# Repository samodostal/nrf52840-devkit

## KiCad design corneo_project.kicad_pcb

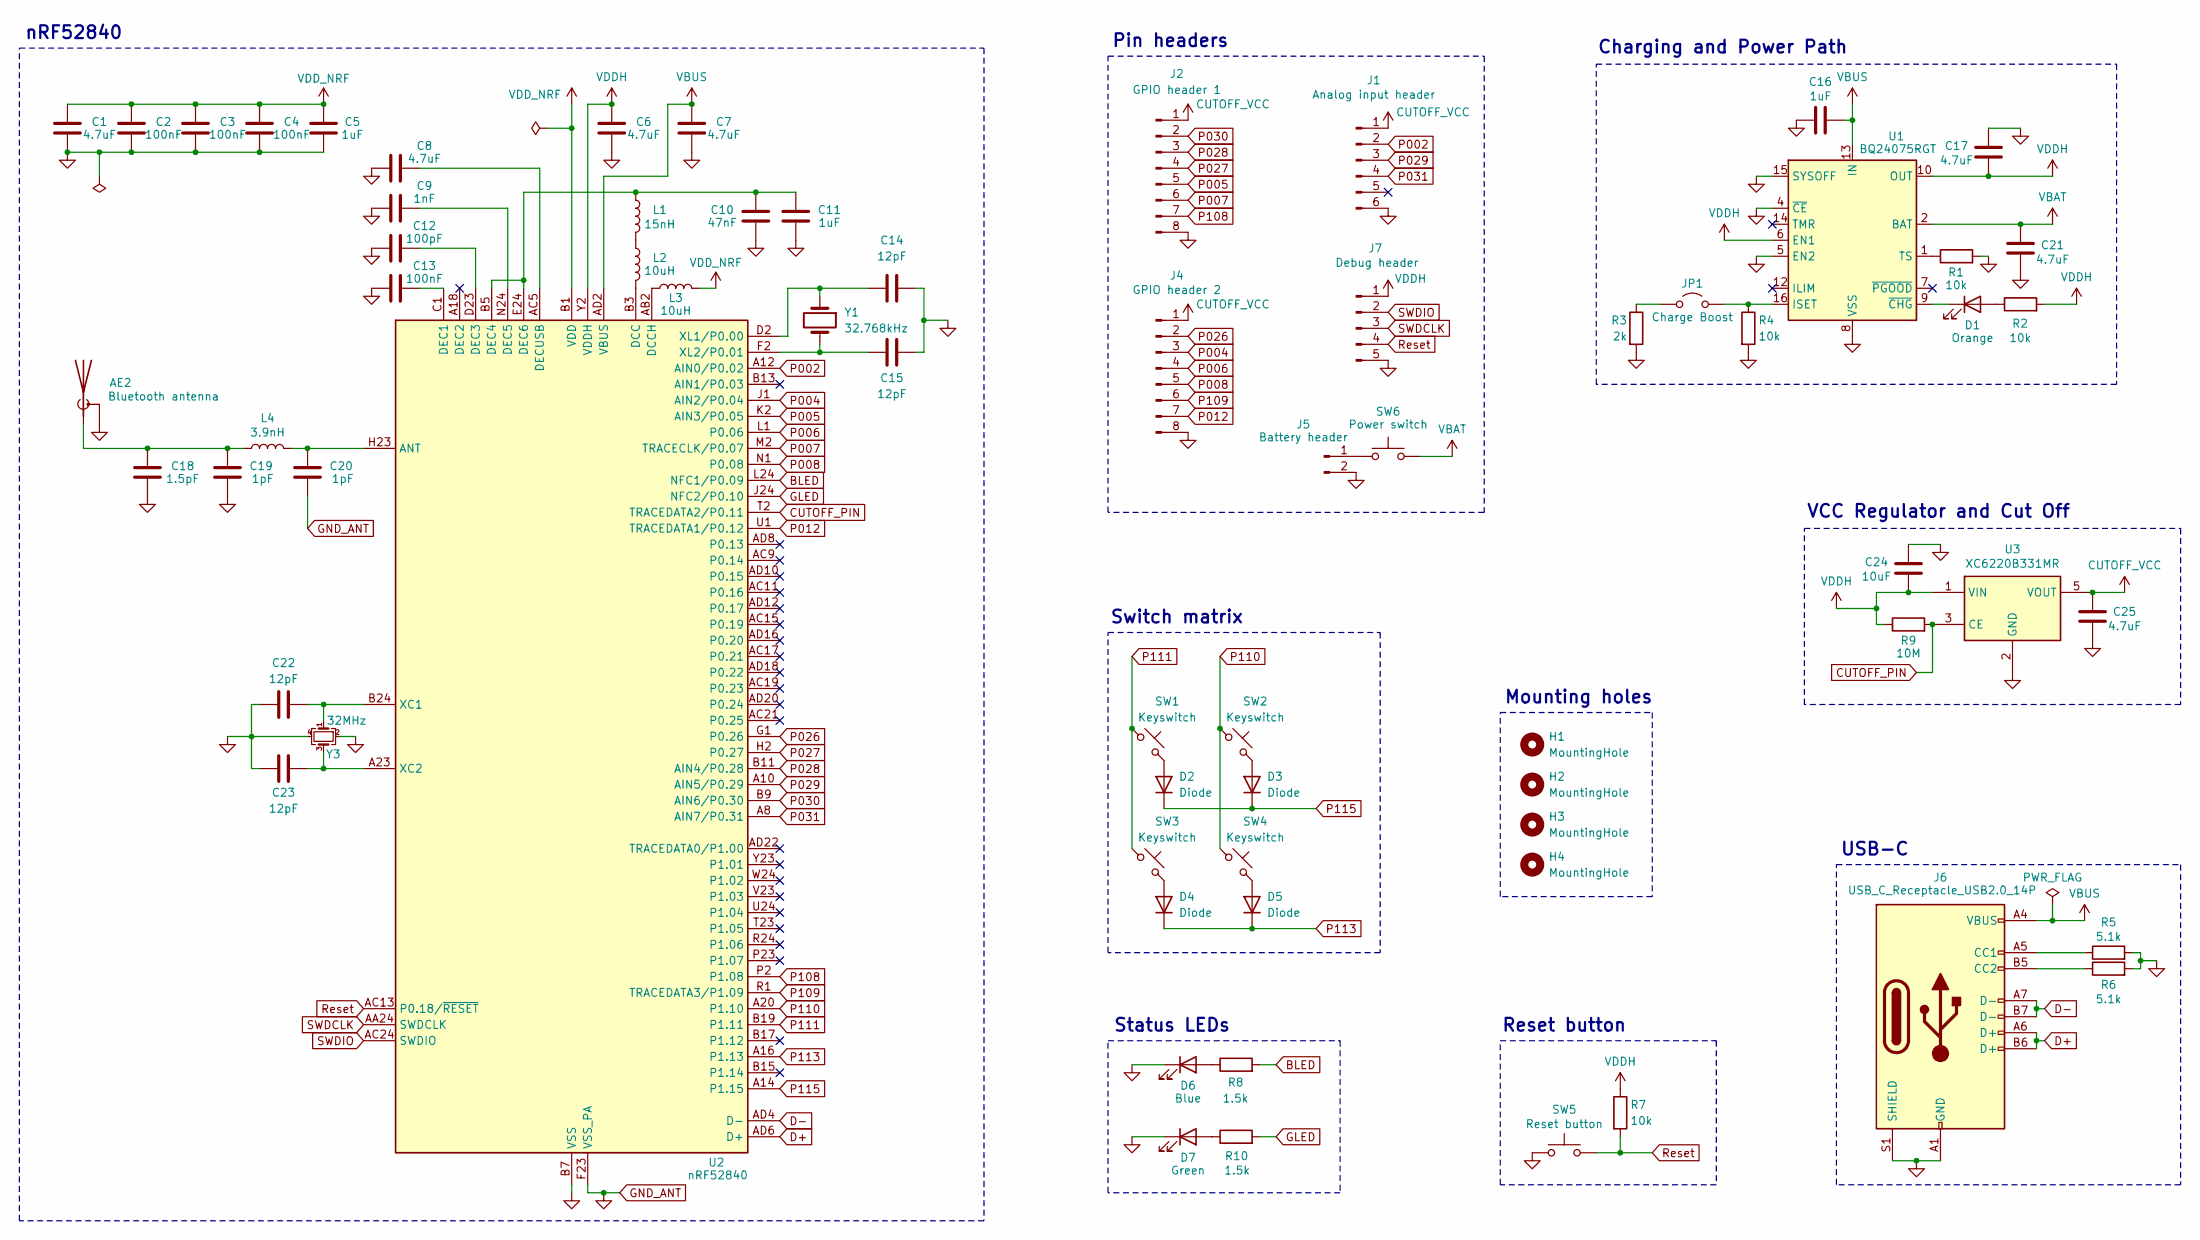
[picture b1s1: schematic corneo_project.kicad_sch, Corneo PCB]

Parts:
AE2: Bluetooth antenna; Texas_SWRA117D_2.4GHz_Left
C1, C6, C7, C8, C17, C21, C25: 4.7uF; C_0805_2012Metric; jlcpcb C1779
C2, C3, C4, C13: 100nF; C_0603_1608Metric; jlcpcb C14663
C5, C11, C16: 1uF; C_0603_1608Metric; jlcpcb C15849
C9: 1nF; C_0603_1608Metric; jlcpcb C1588
C10: 47nF; C_0603_1608Metric; jlcpcb C1622
C12: 100pF; C_0603_1608Metric; jlcpcb C14858
C14, C15, C22, C23: 12pF; C_0603_1608Metric; jlcpcb C38523
C18: 1.5pF; C_0402_1005Metric; jlcpcb C1552
C19, C20: 1pF; C_0402_1005Metric; jlcpcb C1550
C24: 10uF; C_0805_2012Metric; jlcpcb C15850
D1: Orange; LED_0402_1005Metric; jlcpcb C364554
D2, D3, D4, D5: Diode; D_DO-35_SOD27_P7.62mm_Horizontal; JLCPCB_IGNORE 0
D6: Blue; LED_0402_1005Metric; jlcpcb C364550
D7: Green; LED_0402_1005Metric; jlcpcb C364551
H1, H2, H3, H4: MountingHole; MountingHole_2.2mm_M2
J1: Analog input header; PinHeader_1x06_P2.54mm_Vertical; JLCPCB_IGNORE 0
J2: GPIO header 1; PinHeader_1x08_P2.54mm_Vertical; JLCPCB_IGNORE 0
J4: GPIO header 2; PinHeader_1x08_P2.54mm_Vertical; JLCPCB_IGNORE 0
J5: Battery header; PinHeader_1x02_P2.54mm_Vertical; JLCPCB_IGNORE 0
J6: USB_C_Receptacle_USB2.0_14P; USB_C_Receptacle_GCT_USB4105-xx-A_16P_TopMnt_Horizontal; jlcpcb C165948
J7: Debug header; PinHeader_1x05_P2.54mm_Vertical; JLCPCB_IGNORE 0
JP1: Charge Boost; SolderJumper-2_P1.3mm_Open_RoundedPad1.0x1.5mm
L1: 15nH; L_01005_0402Metric; jlcpcb C27143
L2, L3: 10uH; L_0603_1608Metric; jlcpcb C1035
L4: 3.9nH; L_01005_0402Metric; jlcpcb C14033
R1, R2, R4, R7: 10k; R_0603_1608Metric; jlcpcb C25804
R3: 2k; R_0603_1608Metric; jlcpcb C22975
R5, R6: 5.1k; R_0603_1608Metric; jlcpcb C23186
R8, R10: 1.5k; R_0603_1608Metric; jlcpcb C22843
R9: 10M; R_0603_1608Metric; jlcpcb C7250
SW1, SW2, SW3, SW4: Keyswitch; SW_PUSH_6mm; JLCPCB_IGNORE 0
SW5: Reset button; SW_PUSH_6mm; JLCPCB_IGNORE 0
SW6: Power switch; SW_SPDT_PCM12; JLCPCB_IGNORE 0
U1: BQ24075RGT; VQFN-16-1EP_3x3mm_P0.5mm_EP1.6x1.6mm; jlcpcb C15464
U2: nRF52840; Nordic_AQFN-73-1EP_7x7mm_P0.5mm; jlcpcb C190794
U3: XC6220B331MR; SOT-23-5; jlcpcb C86534
Y1: 32.768kHz; Crystal_SMD_2012-2Pin_2.0x1.2mm; jlcpcb C97604
Y3: 32MHz; Crystal_SMD_2016-4Pin_2.0x1.6mm; Manufacturer Part Q22FA1280001800; LCSC Part C255896

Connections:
BLED: R8.2, U2.L24 (NFC1/P0.09)
CUTOFF_PIN: R9.2, U2.T2 (TRACEDATA2/P0.11), U3.3 (CE)
CUTOFF_VCC: C25.2, J1.1, J2.1, J4.1, U3.5 (VOUT)
D+: J6.A6 (D+), J6.B6 (D+), U2.AD6 (D+)
D-: J6.A7 (D-), J6.B7 (D-), U2.AD4 (D-)
GLED: R10.2, U2.J24 (NFC2/P0.10)
GND_ANT: AE2.2 (Shield), C1.1, C2.1, C3.1, C4.1, C5.1, C6.1, C7.1, C8.1, C9.1, C10.1, C11.1, C12.1, C13.1, C14.2, C15.2, C16.1, C17.2, C18.1, C19.1, C20.1, C21.1, C22.2, C23.2, C24.2, C25.1, D6.1 (K), D7.1 (K), J1.6, J2.8, J4.8, J5.2, J6.A1 (GND), J6.A12 (GND), J6.B1 (GND), J6.B12 (GND), J6.S1 (SHIELD), J7.5, R1.2, R3.2, R4.2, R5.2, R6.2, SW5.1, U1.4 (~CE), U1.5 (EN2), U1.8 (VSS), U1.15 (SYSOFF), U1.17 (VSS), U2.B7 (VSS), U2.EP (VSS), U2.F23 (VSS_PA), U3.2 (GND), Y3.2, Y3.4
unnamed: AE2.1 (A), C18.2, C19.2, L4.1
unnamed: D1.2 (A), R2.1
unnamed: D1.1 (K), U1.9 (~CHG)
unnamed: D2.2 (A), SW1.2
unnamed: D3.2 (A), SW2.2
unnamed: D4.2 (A), SW3.2
unnamed: D5.2 (A), SW4.2
unnamed: D6.2 (A), R8.1
unnamed: D7.2 (A), R10.1
unnamed: J5.1, SW6.1
unnamed: J6.A5 (CC1), R5.1
unnamed: J6.B5 (CC2), R6.1
unnamed: JP1.1 (A), R3.1
unnamed: JP1.2 (B), R4.1, U1.16 (ISET)
unnamed: L1.2, L2.1
unnamed: R1.1, U1.1 (TS)
unnamed: C20.2, L4.2, U2.H23 (ANT)
unnamed: L2.2, U2.B3 (DCC)
unnamed: L3.1, U2.AB2 (DCCH)
unnamed: C13.2, U2.C1 (DEC1)
unnamed: C12.2, U2.D23 (DEC3)
unnamed: C10.2, C11.2, L1.1, U2.B5 (DEC4), U2.E24 (DEC6)
unnamed: C9.2, U2.N24 (DEC5)
unnamed: C8.2, U2.AC5 (DECUSB)
unnamed: C22.1, U2.B24 (XC1), Y3.1
unnamed: C23.1, U2.A23 (XC2), Y3.3
unnamed: C14.1, U2.D2 (XL1/P0.00), Y1.1
unnamed: C15.1, U2.F2 (XL2/P0.01), Y1.2
P002: J1.2, U2.A12 (AIN0/P0.02)
P004: J4.3, U2.J1 (AIN2/P0.04)
P005: J2.5, U2.K2 (AIN3/P0.05)
P006: J4.4, U2.L1 (P0.06)
P007: J2.6, U2.M2 (TRACECLK/P0.07)
P008: J4.5, U2.N1 (P0.08)
P012: J4.7, U2.U1 (TRACEDATA1/P0.12)
P026: J4.2, U2.G1 (P0.26)
P027: J2.4, U2.H2 (P0.27)
P028: J2.3, U2.B11 (AIN4/P0.28)
P029: J1.3, U2.A10 (AIN5/P0.29)
P030: J2.2, U2.B9 (AIN6/P0.30)
P031: J1.4, U2.A8 (AIN7/P0.31)
P108: J2.7, U2.P2 (P1.08)
P109: J4.6, U2.R1 (TRACEDATA3/P1.09)
P110: SW2.1, SW4.1, U2.A20 (P1.10)
P111: SW1.1, SW3.1, U2.B19 (P1.11)
P113: D4.1 (K), D5.1 (K), U2.A16 (P1.13)
P115: D2.1 (K), D3.1 (K), U2.A14 (P1.15)
Reset: J7.4, R7.2, SW5.2, U2.AC13 (P0.18/~RESET)
SWDCLK: J7.3, U2.AA24 (SWDCLK)
SWDIO: J7.2, U2.AC24 (SWDIO)
VBAT: C21.2, SW6.2, U1.2 (BAT), U1.3 (BAT)
VBUS: C7.2, C16.2, J6.A4 (VBUS), J6.A9 (VBUS), J6.B4 (VBUS), J6.B9 (VBUS), U1.13 (IN), U2.AD2 (VBUS)
VDDH: C6.2, C17.1, C24.1, J7.1, R2.2, R7.1, R9.1, U1.6 (EN1), U1.10 (OUT), U1.11 (OUT), U2.Y2 (VDDH), U3.1 (VIN)
VDD_NRF: C1.2, C2.2, C3.2, C4.2, C5.2, L3.2, U2.A22 (VDD), U2.AD14 (VDD), U2.AD23 (VDD), U2.B1 (VDD), U2.W1 (VDD)

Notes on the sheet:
Charging and Power Path
nRF52840
Switch matrix
Pin headers
USB-C
VCC Regulator and Cut Off
Reset button
Status LEDs
Mounting holes

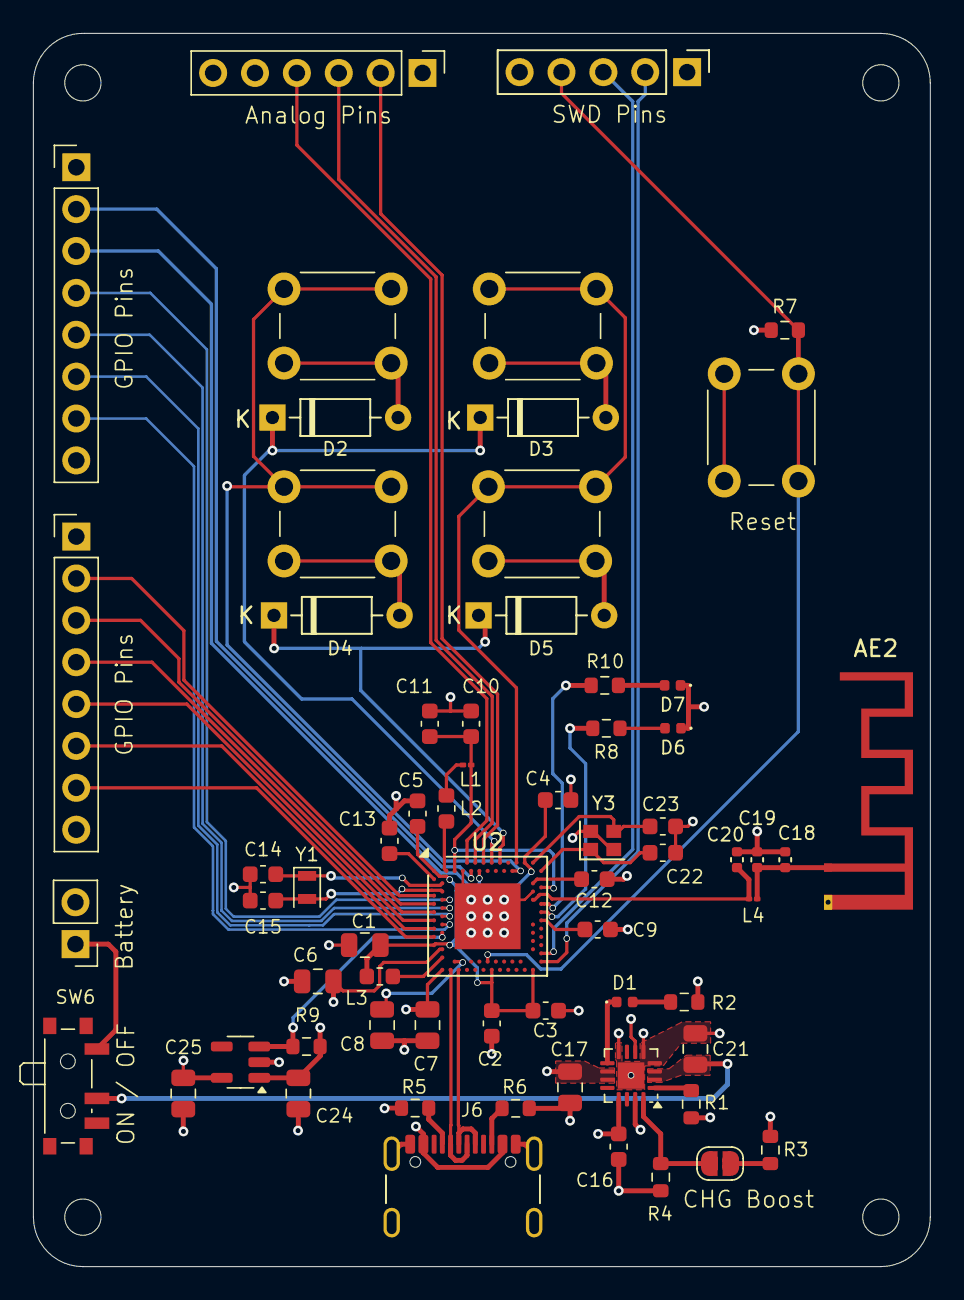
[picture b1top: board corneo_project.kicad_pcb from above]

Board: 4 copper layers, 54.4 x 74.8 mm, 69 parts (0 on the bottom side), 61 nets.

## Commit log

2024-11-13 backup commit
2024-12-02 Connectd unconnected pins
